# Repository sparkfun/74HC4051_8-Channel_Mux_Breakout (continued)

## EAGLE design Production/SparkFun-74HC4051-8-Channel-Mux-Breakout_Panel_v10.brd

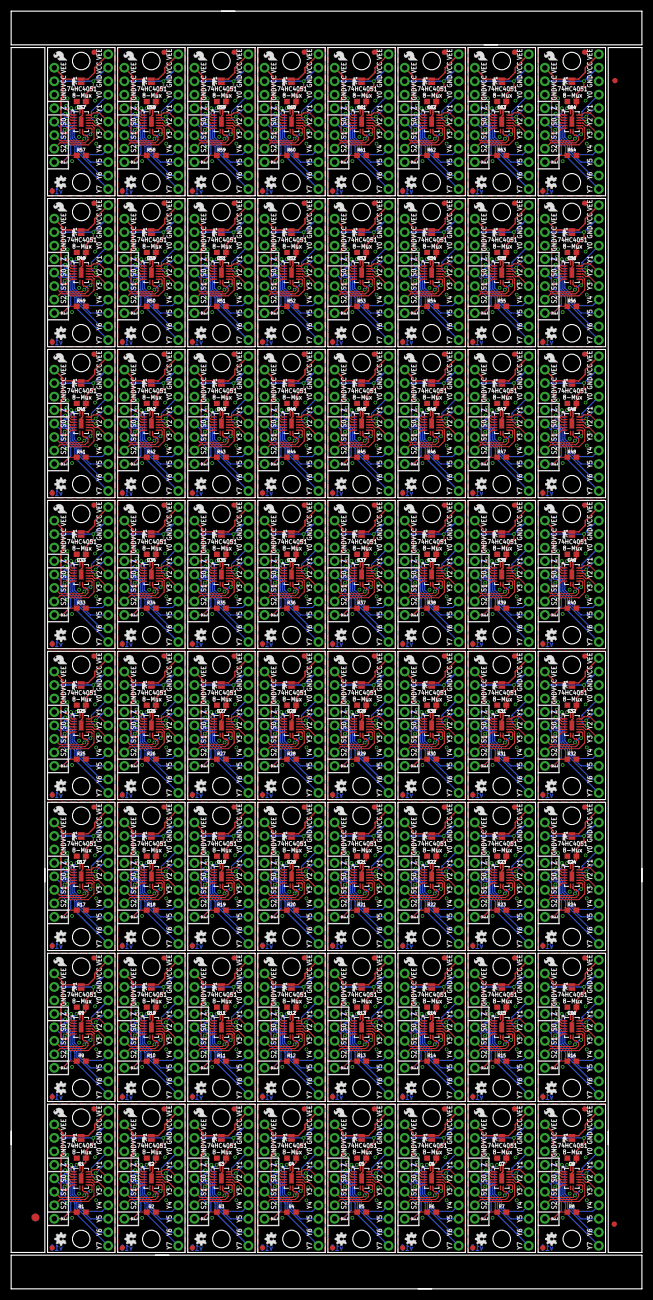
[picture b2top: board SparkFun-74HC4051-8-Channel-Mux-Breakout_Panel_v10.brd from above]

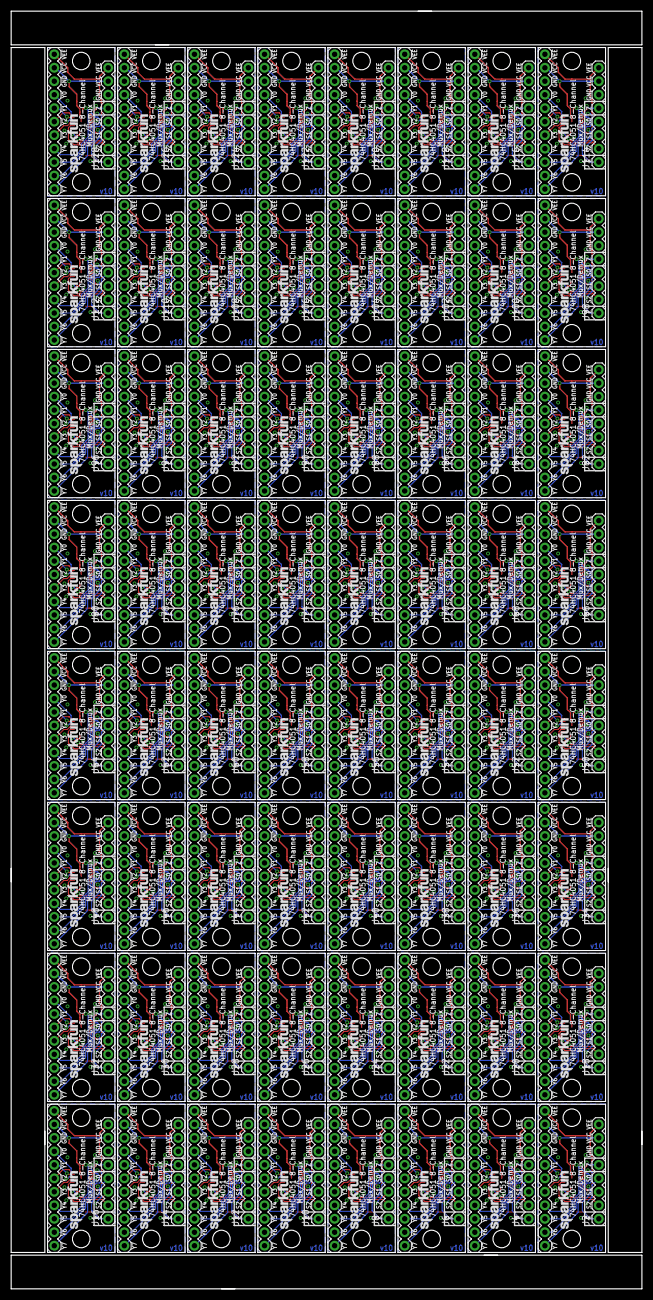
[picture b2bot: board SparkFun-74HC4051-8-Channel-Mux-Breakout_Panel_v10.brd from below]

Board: 2 copper layers, 118.9 x 240.8 mm, 835 parts (192 on the bottom side), 1024 nets.

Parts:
C1, C2, C3, C4, C5, C6, C7, C8, C9, C10, C11, C12, C13, C14, C15, C16, C17, C18, C19, C20, C21, C22, C23, C24, C25, C26, C27, C28, C29, C30, C31, C32, C33, C34, C35, C36, C37, C38, C39, C40, C41, C42, C43, C44, C45, C46, C47, C48, C49, C50, C51, C52, C53, C54, C55, C56, C57, C58, C59, C60, C61, C62, C63, C64: 0.1uF; 0603
E$1: FIDUCIAL-1.5X3
E$5, E$7: FIDUCIAL-1X2
FD1, FD2, FD3, FD4, FD5, FD6, FD7, FD8, FD9, FD10, FD11, FD12, FD13, FD14, FD15, FD16, FD17, FD18, FD19, FD20, FD21, FD22, FD23, FD24, FD25, FD26, FD27, FD28, FD29, FD30, FD31, FD32, FD33, FD34, FD35, FD36, FD37, FD38, FD39, FD40, FD41, FD42, FD43, FD44, FD45, FD46, FD47, FD48, FD49, FD50, FD51, FD52, FD53, FD54, FD55, FD56, FD57, FD58, FD59, FD60, FD61, FD62, FD63, FD64, FD65, FD66, FD67, FD68, FD69, FD70, FD71, FD72, FD73, FD74, FD75, FD76, FD77, FD78, FD79, FD80, FD81, FD82, FD83, FD84, FD85, FD86, FD87, FD88, FD89, FD90, FD91, FD92, FD93, FD94, FD95, FD96, FD97, FD98, FD99, FD100, FD101, FD102, FD103, FD104, FD105, FD106, FD107, FD108, FD109, FD110, FD111, FD112, FD113, FD114, FD115, FD116, FD117, FD118, FD119, FD120, FD121, FD122, FD123, FD124, FD125, FD126, FD127, FD128: FIDUCIAL1X2; FIDUCIAL-1X2
H1, H2, H3, H4, H5, H6, H7, H8, H9, H10, H11, H12, H13, H14, H15, H16, H17, H18, H19, H20, H21, H22, H23, H24, H25, H26, H27, H28, H29, H30, H31, H32, H33, H34, H35, H36, H37, H38, H39, H40, H41, H42, H43, H44, H45, H46, H47, H48, H49, H50, H51, H52, H53, H54, H55, H56, H57, H58, H59, H60, H61, H62, H63, H64, H65, H66, H67, H68, H69, H70, H71, H72, H73, H74, H75, H76, H77, H78, H79, H80, H81, H82, H83, H84, H85, H86, H87, H88, H89, H90, H91, H92, H93, H94, H95, H96, H97, H98, H99, H100, H101, H102, H103, H104, H105, H106, H107, H108, H109, H110, H111, H112, H113, H114, H115, H116, H117, H118, H119, H120, H121, H122, H123, H124, H125, H126, H127, H128: STAND-OFF
J1, J3, J5, J7, J9, J11, J13, J15, J17, J19, J21, J23, J25, J27, J29, J31, J33, J35, J37, J39, J41, J43, J45, J47, J49, J51, J53, J55, J57, J59, J61, J63, J65, J67, J69, J71, J73, J75, J77, J79, J81, J83, J85, J87, J89, J91, J93, J95, J97, J99, J101, J103, J105, J107, J109, J111, J113, J115, J117, J119, J121, J123, J125, J127: 1X11
J2, J4, J6, J8, J10, J12, J14, J16, J18, J20, J22, J24, J26, J28, J30, J32, J34, J36, J38, J40, J42, J44, J46, J48, J50, J52, J54, J56, J58, J60, J62, J64, J66, J68, J70, J72, J74, J76, J78, J80, J82, J84, J86, J88, J90, J92, J94, J96, J98, J100, J102, J104, J106, J108, J110, J112, J114, J116, J118, J120, J122, J124, J126, J128: 1X08_ROUND
JP1, JP2, JP3, JP4, JP5, JP6, JP7, JP8, JP9, JP10, JP11, JP12, JP13, JP14, JP15, JP16, JP17, JP18, JP19, JP20, JP21, JP22, JP23, JP24, JP25, JP26, JP27, JP28, JP29, JP30, JP31, JP32, JP33, JP34, JP35, JP36, JP37, JP38, JP39, JP40, JP41, JP42, JP43, JP44, JP45, JP46, JP47, JP48, JP49, JP50, JP51, JP52, JP53, JP54, JP55, JP56, JP57, JP58, JP59, JP60, JP61, JP62, JP63, JP64: VEE-GND; PAD-JUMPER-2-NC_BY_PASTE_NO_SILK
LOGO1, LOGO4, LOGO7, LOGO10, LOGO13, LOGO16, LOGO19, LOGO22, LOGO25, LOGO28, LOGO31, LOGO34, LOGO37, LOGO40, LOGO43, LOGO46, LOGO49, LOGO52, LOGO55, LOGO58, LOGO61, LOGO64, LOGO67, LOGO70, LOGO73, LOGO76, LOGO79, LOGO82, LOGO85, LOGO88, LOGO91, LOGO94, LOGO97, LOGO100, LOGO103, LOGO106, LOGO109, LOGO112, LOGO115, LOGO118, LOGO121, LOGO124, LOGO127, LOGO130, LOGO133, LOGO136, LOGO139, LOGO142, LOGO145, LOGO148, LOGO151, LOGO154, LOGO157, LOGO160, LOGO163, LOGO166, LOGO169, LOGO172, LOGO175, LOGO178, LOGO181, LOGO184, LOGO187, LOGO190: SFE_LOGO_FLAME.1_INCH; SFE_LOGO_FLAME_.1
LOGO2, LOGO5, LOGO8, LOGO11, LOGO14, LOGO17, LOGO20, LOGO23, LOGO26, LOGO29, LOGO32, LOGO35, LOGO38, LOGO41, LOGO44, LOGO47, LOGO50, LOGO53, LOGO56, LOGO59, LOGO62, LOGO65, LOGO68, LOGO71, LOGO74, LOGO77, LOGO80, LOGO83, LOGO86, LOGO89, LOGO92, LOGO95, LOGO98, LOGO101, LOGO104, LOGO107, LOGO110, LOGO113, LOGO116, LOGO119, LOGO122, LOGO125, LOGO128, LOGO131, LOGO134, LOGO137, LOGO140, LOGO143, LOGO146, LOGO149, LOGO152, LOGO155, LOGO158, LOGO161, LOGO164, LOGO167, LOGO170, LOGO173, LOGO176, LOGO179, LOGO182, LOGO185, LOGO188, LOGO191: OSHW-LOGOMINI; OSHW-LOGO-MINI
LOGO3, LOGO6, LOGO9, LOGO12, LOGO15, LOGO18, LOGO21, LOGO24, LOGO27, LOGO30, LOGO33, LOGO36, LOGO39, LOGO42, LOGO45, LOGO48, LOGO51, LOGO54, LOGO57, LOGO60, LOGO63, LOGO66, LOGO69, LOGO72, LOGO75, LOGO78, LOGO81, LOGO84, LOGO87, LOGO90, LOGO93, LOGO96, LOGO99, LOGO102, LOGO105, LOGO108, LOGO111, LOGO114, LOGO117, LOGO120, LOGO123, LOGO126, LOGO129, LOGO132, LOGO135, LOGO138, LOGO141, LOGO144, LOGO147, LOGO150, LOGO153, LOGO156, LOGO159, LOGO162, LOGO165, LOGO168, LOGO171, LOGO174, LOGO177, LOGO180, LOGO183, LOGO186, LOGO189, LOGO192: SFE_LOGO_NAME.1_INCH; SFE_LOGO_NAME_.1
R1, R2, R3, R4, R5, R6, R7, R8, R9, R10, R11, R12, R13, R14, R15, R16, R17, R18, R19, R20, R21, R22, R23, R24, R25, R26, R27, R28, R29, R30, R31, R32, R33, R34, R35, R36, R37, R38, R39, R40, R41, R42, R43, R44, R45, R46, R47, R48, R49, R50, R51, R52, R53, R54, R55, R56, R57, R58, R59, R60, R61, R62, R63, R64: 10k; 0603
U1, U2, U3, U4, U5, U6, U7, U8, U9, U10, U11, U12, U13, U14, U15, U16, U17, U18, U19, U20, U21, U22, U23, U24, U25, U26, U27, U28, U29, U30, U31, U32, U33, U34, U35, U36, U37, U38, U39, U40, U41, U42, U43, U44, U45, U46, U47, U48, U49, U50, U51, U52, U53, U54, U55, U56, U57, U58, U59, U60, U61, U62, U63, U64: 74HC4051BQ; DHVQFN-16-2.5X3.5MM

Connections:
!E!: J2.1, R1.1, U1.6
!E!1: J4.1, R2.1, U2.6
!E!2: J6.1, R3.1, U3.6
!E!3: J8.1, R4.1, U4.6
!E!4: J10.1, R5.1, U5.6
!E!5: J12.1, R6.1, U6.6
!E!6: J14.1, R7.1, U7.6
!E!7: J16.1, R8.1, U8.6
!E!8: J18.1, R9.1, U9.6
!E!9: J20.1, R10.1, U10.6
!E!10: J22.1, R11.1, U11.6
!E!11: J24.1, R12.1, U12.6
!E!12: J26.1, R13.1, U13.6
!E!13: J28.1, R14.1, U14.6
!E!14: J30.1, R15.1, U15.6
!E!15: J32.1, R16.1, U16.6
!E!16: J34.1, R17.1, U17.6
!E!17: J36.1, R18.1, U18.6
!E!18: J38.1, R19.1, U19.6
!E!19: J40.1, R20.1, U20.6
!E!20: J42.1, R21.1, U21.6
!E!21: J44.1, R22.1, U22.6
!E!22: J46.1, R23.1, U23.6
!E!23: J48.1, R24.1, U24.6
!E!24: J50.1, R25.1, U25.6
!E!25: J52.1, R26.1, U26.6
!E!26: J54.1, R27.1, U27.6
!E!27: J56.1, R28.1, U28.6
!E!28: J58.1, R29.1, U29.6
!E!29: J60.1, R30.1, U30.6
!E!30: J62.1, R31.1, U31.6
!E!31: J64.1, R32.1, U32.6
!E!32: J66.1, R33.1, U33.6
!E!33: J68.1, R34.1, U34.6
!E!34: J70.1, R35.1, U35.6
!E!35: J72.1, R36.1, U36.6
!E!36: J74.1, R37.1, U37.6
!E!37: J76.1, R38.1, U38.6
!E!38: J78.1, R39.1, U39.6
!E!39: J80.1, R40.1, U40.6
!E!40: J82.1, R41.1, U41.6
!E!41: J84.1, R42.1, U42.6
!E!42: J86.1, R43.1, U43.6
!E!43: J88.1, R44.1, U44.6
!E!44: J90.1, R45.1, U45.6
!E!45: J92.1, R46.1, U46.6
!E!46: J94.1, R47.1, U47.6
!E!47: J96.1, R48.1, U48.6
!E!48: J98.1, R49.1, U49.6
!E!49: J100.1, R50.1, U50.6
!E!50: J102.1, R51.1, U51.6
!E!51: J104.1, R52.1, U52.6
!E!52: J106.1, R53.1, U53.6
!E!53: J108.1, R54.1, U54.6
!E!54: J110.1, R55.1, U55.6
!E!55: J112.1, R56.1, U56.6
!E!56: J114.1, R57.1, U57.6
!E!57: J116.1, R58.1, U58.6
!E!58: J118.1, R59.1, U59.6
!E!59: J120.1, R60.1, U60.6
!E!60: J122.1, R61.1, U61.6
!E!61: J124.1, R62.1, U62.6
!E!62: J126.1, R63.1, U63.6
!E!63: J128.1, R64.1, U64.6
GND: C1.2, J1.9, J2.6, JP1.1, R1.2, U1.8
GND1: C2.2, J3.9, J4.6, JP2.1, R2.2, U2.8
GND2: C3.2, J5.9, J6.6, JP3.1, R3.2, U3.8
GND3: C4.2, J7.9, J8.6, JP4.1, R4.2, U4.8
GND4: C5.2, J9.9, J10.6, JP5.1, R5.2, U5.8
GND5: C6.2, J11.9, J12.6, JP6.1, R6.2, U6.8
GND6: C7.2, J13.9, J14.6, JP7.1, R7.2, U7.8
GND7: C8.2, J15.9, J16.6, JP8.1, R8.2, U8.8
GND8: C9.2, J17.9, J18.6, JP9.1, R9.2, U9.8
GND9: C10.2, J19.9, J20.6, JP10.1, R10.2, U10.8
GND10: C11.2, J21.9, J22.6, JP11.1, R11.2, U11.8
GND11: C12.2, J23.9, J24.6, JP12.1, R12.2, U12.8
GND12: C13.2, J25.9, J26.6, JP13.1, R13.2, U13.8
GND13: C14.2, J27.9, J28.6, JP14.1, R14.2, U14.8
GND14: C15.2, J29.9, J30.6, JP15.1, R15.2, U15.8
GND15: C16.2, J31.9, J32.6, JP16.1, R16.2, U16.8
GND16: C17.2, J33.9, J34.6, JP17.1, R17.2, U17.8
GND17: C18.2, J35.9, J36.6, JP18.1, R18.2, U18.8
GND18: C19.2, J37.9, J38.6, JP19.1, R19.2, U19.8
GND19: C20.2, J39.9, J40.6, JP20.1, R20.2, U20.8
GND20: C21.2, J41.9, J42.6, JP21.1, R21.2, U21.8
GND21: C22.2, J43.9, J44.6, JP22.1, R22.2, U22.8
GND22: C23.2, J45.9, J46.6, JP23.1, R23.2, U23.8
GND23: C24.2, J47.9, J48.6, JP24.1, R24.2, U24.8
GND24: C25.2, J49.9, J50.6, JP25.1, R25.2, U25.8
GND25: C26.2, J51.9, J52.6, JP26.1, R26.2, U26.8
GND26: C27.2, J53.9, J54.6, JP27.1, R27.2, U27.8
GND27: C28.2, J55.9, J56.6, JP28.1, R28.2, U28.8
GND28: C29.2, J57.9, J58.6, JP29.1, R29.2, U29.8
GND29: C30.2, J59.9, J60.6, JP30.1, R30.2, U30.8
GND30: C31.2, J61.9, J62.6, JP31.1, R31.2, U31.8
GND31: C32.2, J63.9, J64.6, JP32.1, R32.2, U32.8
GND32: C33.2, J65.9, J66.6, JP33.1, R33.2, U33.8
GND33: C34.2, J67.9, J68.6, JP34.1, R34.2, U34.8
GND34: C35.2, J69.9, J70.6, JP35.1, R35.2, U35.8
GND35: C36.2, J71.9, J72.6, JP36.1, R36.2, U36.8
GND36: C37.2, J73.9, J74.6, JP37.1, R37.2, U37.8
GND37: C38.2, J75.9, J76.6, JP38.1, R38.2, U38.8
GND38: C39.2, J77.9, J78.6, JP39.1, R39.2, U39.8
GND39: C40.2, J79.9, J80.6, JP40.1, R40.2, U40.8
GND40: C41.2, J81.9, J82.6, JP41.1, R41.2, U41.8
GND41: C42.2, J83.9, J84.6, JP42.1, R42.2, U42.8
GND42: C43.2, J85.9, J86.6, JP43.1, R43.2, U43.8
GND43: C44.2, J87.9, J88.6, JP44.1, R44.2, U44.8
GND44: C45.2, J89.9, J90.6, JP45.1, R45.2, U45.8
GND45: C46.2, J91.9, J92.6, JP46.1, R46.2, U46.8
GND46: C47.2, J93.9, J94.6, JP47.1, R47.2, U47.8
GND47: C48.2, J95.9, J96.6, JP48.1, R48.2, U48.8
GND48: C49.2, J97.9, J98.6, JP49.1, R49.2, U49.8
GND49: C50.2, J99.9, J100.6, JP50.1, R50.2, U50.8
GND50: C51.2, J101.9, J102.6, JP51.1, R51.2, U51.8
GND51: C52.2, J103.9, J104.6, JP52.1, R52.2, U52.8
GND52: C53.2, J105.9, J106.6, JP53.1, R53.2, U53.8
GND53: C54.2, J107.9, J108.6, JP54.1, R54.2, U54.8
GND54: C55.2, J109.9, J110.6, JP55.1, R55.2, U55.8
GND55: C56.2, J111.9, J112.6, JP56.1, R56.2, U56.8
GND56: C57.2, J113.9, J114.6, JP57.1, R57.2, U57.8
GND57: C58.2, J115.9, J116.6, JP58.1, R58.2, U58.8
GND58: C59.2, J117.9, J118.6, JP59.1, R59.2, U59.8
GND59: C60.2, J119.9, J120.6, JP60.1, R60.2, U60.8
GND60: C61.2, J121.9, J122.6, JP61.1, R61.2, U61.8
GND61: C62.2, J123.9, J124.6, JP62.1, R62.2, U62.8
GND62: C63.2, J125.9, J126.6, JP63.1, R63.2, U63.8
GND63: C64.2, J127.9, J128.6, JP64.1, R64.2, U64.8
S0: J2.4, U1.11
S1: J2.3, U1.10
S2: J2.2, U1.9
S3: J4.2, U2.9
S4: J4.4, U2.11
S5: J4.3, U2.10
S6: J6.2, U3.9
S7: J6.4, U3.11
S8: J6.3, U3.10
S9: J8.2, U4.9
S10: J8.4, U4.11
S11: J8.3, U4.10
S12: J10.2, U5.9
S13: J10.4, U5.11
S14: J10.3, U5.10
S15: J12.2, U6.9
S16: J12.4, U6.11
S17: J12.3, U6.10
S18: J14.2, U7.9
S19: J14.4, U7.11
S20: J14.3, U7.10
S21: J16.2, U8.9
S22: J16.4, U8.11
S23: J16.3, U8.10
S24: J18.2, U9.9
S25: J18.4, U9.11
S26: J18.3, U9.10
S27: J20.2, U10.9
S28: J20.4, U10.11
S29: J20.3, U10.10
S30: J22.2, U11.9
S31: J22.4, U11.11
S32: J22.3, U11.10
S33: J24.2, U12.9
S34: J24.4, U12.11
S35: J24.3, U12.10
S36: J26.2, U13.9
S37: J26.4, U13.11
S38: J26.3, U13.10
S39: J28.2, U14.9
S40: J28.4, U14.11
S41: J28.3, U14.10
S42: J30.2, U15.9
S43: J30.4, U15.11
S44: J30.3, U15.10
S45: J32.2, U16.9
S46: J32.4, U16.11
S47: J32.3, U16.10
S48: J34.2, U17.9
S49: J34.4, U17.11
S50: J34.3, U17.10
S51: J36.2, U18.9
S52: J36.4, U18.11
S53: J36.3, U18.10
S54: J38.2, U19.9
S55: J38.4, U19.11
S56: J38.3, U19.10
S57: J40.2, U20.9
S58: J40.4, U20.11
S59: J40.3, U20.10
S60: J42.2, U21.9
S61: J42.4, U21.11
S62: J42.3, U21.10
S63: J44.2, U22.9
S64: J44.4, U22.11
S65: J44.3, U22.10
S66: J46.2, U23.9
S67: J46.4, U23.11
S68: J46.3, U23.10
S69: J48.2, U24.9
S70: J48.4, U24.11
S71: J48.3, U24.10
S72: J50.2, U25.9
S73: J50.4, U25.11
S74: J50.3, U25.10
S75: J52.2, U26.9
S76: J52.4, U26.11
S77: J52.3, U26.10
S78: J54.2, U27.9
S79: J54.4, U27.11
S80: J54.3, U27.10
S81: J56.2, U28.9
S82: J56.4, U28.11
S83: J56.3, U28.10
S84: J58.2, U29.9
S85: J58.4, U29.11
S86: J58.3, U29.10
S87: J60.2, U30.9
S88: J60.4, U30.11
S89: J60.3, U30.10
S90: J62.2, U31.9
S91: J62.4, U31.11
S92: J62.3, U31.10
S93: J64.2, U32.9
S94: J64.4, U32.11
S95: J64.3, U32.10
S96: J66.2, U33.9
S97: J66.4, U33.11
S98: J66.3, U33.10
S99: J68.2, U34.9
S100: J68.4, U34.11
S101: J68.3, U34.10
S102: J70.2, U35.9
S103: J70.4, U35.11
S104: J70.3, U35.10
S105: J72.2, U36.9
S106: J72.4, U36.11
S107: J72.3, U36.10
S108: J74.2, U37.9
S109: J74.4, U37.11
S110: J74.3, U37.10
S111: J76.2, U38.9
S112: J76.4, U38.11
S113: J76.3, U38.10
S114: J78.2, U39.9
S115: J78.4, U39.11
S116: J78.3, U39.10
S117: J80.2, U40.9
S118: J80.4, U40.11
S119: J80.3, U40.10
S120: J82.2, U41.9
S121: J82.4, U41.11
S122: J82.3, U41.10
S123: J84.2, U42.9
S124: J84.4, U42.11
S125: J84.3, U42.10
S126: J86.2, U43.9
S127: J86.4, U43.11
S128: J86.3, U43.10
S129: J88.2, U44.9
S130: J88.4, U44.11
S131: J88.3, U44.10
S132: J90.2, U45.9
S133: J90.4, U45.11
S134: J90.3, U45.10
S135: J92.2, U46.9
S136: J92.4, U46.11
S137: J92.3, U46.10
S138: J94.2, U47.9
S139: J94.4, U47.11
S140: J94.3, U47.10
S141: J96.2, U48.9
S142: J96.4, U48.11
S143: J96.3, U48.10
S144: J98.2, U49.9
S145: J98.4, U49.11
S146: J98.3, U49.10
S147: J100.2, U50.9
S148: J100.4, U50.11
S149: J100.3, U50.10
S150: J102.2, U51.9
S151: J102.4, U51.11
S152: J102.3, U51.10
S153: J104.2, U52.9
S154: J104.4, U52.11
S155: J104.3, U52.10
S156: J106.2, U53.9
S157: J106.4, U53.11
S158: J106.3, U53.10
S159: J108.2, U54.9
S160: J108.4, U54.11
S161: J108.3, U54.10
S162: J110.2, U55.9
S163: J110.4, U55.11
S164: J110.3, U55.10
S165: J112.2, U56.9
S166: J112.4, U56.11
S167: J112.3, U56.10
S168: J114.2, U57.9
S169: J114.4, U57.11
S170: J114.3, U57.10
S171: J116.2, U58.9
S172: J116.4, U58.11
S173: J116.3, U58.10
S174: J118.2, U59.9
S175: J118.4, U59.11
S176: J118.3, U59.10
S177: J120.2, U60.9
S178: J120.4, U60.11
S179: J120.3, U60.10
S180: J122.2, U61.9
S181: J122.4, U61.11
S182: J122.3, U61.10
S183: J124.2, U62.9
S184: J124.4, U62.11
S185: J124.3, U62.10
S186: J126.2, U63.9
S187: J126.4, U63.11
S188: J126.3, U63.10
S189: J128.2, U64.9
S190: J128.4, U64.11
S191: J128.3, U64.10
VCC: C1.1, J1.10, J2.7, U1.16, U1.EP
VCC1: C2.1, J3.10, J4.7, U2.16, U2.EP
VCC2: C3.1, J5.10, J6.7, U3.16, U3.EP
VCC3: C4.1, J7.10, J8.7, U4.16, U4.EP
VCC4: C5.1, J9.10, J10.7, U5.16, U5.EP
VCC5: C6.1, J11.10, J12.7, U6.16, U6.EP
VCC6: C7.1, J13.10, J14.7, U7.16, U7.EP
VCC7: C8.1, J15.10, J16.7, U8.16, U8.EP
VCC8: C9.1, J17.10, J18.7, U9.16, U9.EP
VCC9: C10.1, J19.10, J20.7, U10.16, U10.EP
VCC10: C11.1, J21.10, J22.7, U11.16, U11.EP
VCC11: C12.1, J23.10, J24.7, U12.16, U12.EP
VCC12: C13.1, J25.10, J26.7, U13.16, U13.EP
VCC13: C14.1, J27.10, J28.7, U14.16, U14.EP
VCC14: C15.1, J29.10, J30.7, U15.16, U15.EP
VCC15: C16.1, J31.10, J32.7, U16.16, U16.EP
VCC16: C17.1, J33.10, J34.7, U17.16, U17.EP
VCC17: C18.1, J35.10, J36.7, U18.16, U18.EP
VCC18: C19.1, J37.10, J38.7, U19.16, U19.EP
VCC19: C20.1, J39.10, J40.7, U20.16, U20.EP
VCC20: C21.1, J41.10, J42.7, U21.16, U21.EP
VCC21: C22.1, J43.10, J44.7, U22.16, U22.EP
VCC22: C23.1, J45.10, J46.7, U23.16, U23.EP
VCC23: C24.1, J47.10, J48.7, U24.16, U24.EP
VCC24: C25.1, J49.10, J50.7, U25.16, U25.EP
VCC25: C26.1, J51.10, J52.7, U26.16, U26.EP
VCC26: C27.1, J53.10, J54.7, U27.16, U27.EP
VCC27: C28.1, J55.10, J56.7, U28.16, U28.EP
VCC28: C29.1, J57.10, J58.7, U29.16, U29.EP
VCC29: C30.1, J59.10, J60.7, U30.16, U30.EP
VCC30: C31.1, J61.10, J62.7, U31.16, U31.EP
VCC31: C32.1, J63.10, J64.7, U32.16, U32.EP
VCC32: C33.1, J65.10, J66.7, U33.16, U33.EP
VCC33: C34.1, J67.10, J68.7, U34.16, U34.EP
VCC34: C35.1, J69.10, J70.7, U35.16, U35.EP
VCC35: C36.1, J71.10, J72.7, U36.16, U36.EP
VCC36: C37.1, J73.10, J74.7, U37.16, U37.EP
VCC37: C38.1, J75.10, J76.7, U38.16, U38.EP
VCC38: C39.1, J77.10, J78.7, U39.16, U39.EP
VCC39: C40.1, J79.10, J80.7, U40.16, U40.EP
VCC40: C41.1, J81.10, J82.7, U41.16, U41.EP
VCC41: C42.1, J83.10, J84.7, U42.16, U42.EP
VCC42: C43.1, J85.10, J86.7, U43.16, U43.EP
VCC43: C44.1, J87.10, J88.7, U44.16, U44.EP
VCC44: C45.1, J89.10, J90.7, U45.16, U45.EP
VCC45: C46.1, J91.10, J92.7, U46.16, U46.EP
VCC46: C47.1, J93.10, J94.7, U47.16, U47.EP
VCC47: C48.1, J95.10, J96.7, U48.16, U48.EP
VCC48: C49.1, J97.10, J98.7, U49.16, U49.EP
VCC49: C50.1, J99.10, J100.7, U50.16, U50.EP
VCC50: C51.1, J101.10, J102.7, U51.16, U51.EP
VCC51: C52.1, J103.10, J104.7, U52.16, U52.EP
VCC52: C53.1, J105.10, J106.7, U53.16, U53.EP
VCC53: C54.1, J107.10, J108.7, U54.16, U54.EP
VCC54: C55.1, J109.10, J110.7, U55.16, U55.EP
VCC55: C56.1, J111.10, J112.7, U56.16, U56.EP
VCC56: C57.1, J113.10, J114.7, U57.16, U57.EP
VCC57: C58.1, J115.10, J116.7, U58.16, U58.EP
VCC58: C59.1, J117.10, J118.7, U59.16, U59.EP
VCC59: C60.1, J119.10, J120.7, U60.16, U60.EP
VCC60: C61.1, J121.10, J122.7, U61.16, U61.EP
VCC61: C62.1, J123.10, J124.7, U62.16, U62.EP
VCC62: C63.1, J125.10, J126.7, U63.16, U63.EP
VCC63: C64.1, J127.10, J128.7, U64.16, U64.EP
VEE: J1.11, J2.8, JP1.2, U1.7
VEE1: J3.11, J4.8, JP2.2, U2.7
VEE2: J5.11, J6.8, JP3.2, U3.7
VEE3: J7.11, J8.8, JP4.2, U4.7
VEE4: J9.11, J10.8, JP5.2, U5.7
VEE5: J11.11, J12.8, JP6.2, U6.7
VEE6: J13.11, J14.8, JP7.2, U7.7
VEE7: J15.11, J16.8, JP8.2, U8.7
VEE8: J17.11, J18.8, JP9.2, U9.7
VEE9: J19.11, J20.8, JP10.2, U10.7
VEE10: J21.11, J22.8, JP11.2, U11.7
VEE11: J23.11, J24.8, JP12.2, U12.7
VEE12: J25.11, J26.8, JP13.2, U13.7
VEE13: J27.11, J28.8, JP14.2, U14.7
VEE14: J29.11, J30.8, JP15.2, U15.7
VEE15: J31.11, J32.8, JP16.2, U16.7
VEE16: J33.11, J34.8, JP17.2, U17.7
VEE17: J35.11, J36.8, JP18.2, U18.7
VEE18: J37.11, J38.8, JP19.2, U19.7
VEE19: J39.11, J40.8, JP20.2, U20.7
VEE20: J41.11, J42.8, JP21.2, U21.7
VEE21: J43.11, J44.8, JP22.2, U22.7
VEE22: J45.11, J46.8, JP23.2, U23.7
VEE23: J47.11, J48.8, JP24.2, U24.7
VEE24: J49.11, J50.8, JP25.2, U25.7
VEE25: J51.11, J52.8, JP26.2, U26.7
VEE26: J53.11, J54.8, JP27.2, U27.7
VEE27: J55.11, J56.8, JP28.2, U28.7
VEE28: J57.11, J58.8, JP29.2, U29.7
VEE29: J59.11, J60.8, JP30.2, U30.7
VEE30: J61.11, J62.8, JP31.2, U31.7
VEE31: J63.11, J64.8, JP32.2, U32.7
VEE32: J65.11, J66.8, JP33.2, U33.7
VEE33: J67.11, J68.8, JP34.2, U34.7
VEE34: J69.11, J70.8, JP35.2, U35.7
VEE35: J71.11, J72.8, JP36.2, U36.7
VEE36: J73.11, J74.8, JP37.2, U37.7
VEE37: J75.11, J76.8, JP38.2, U38.7
VEE38: J77.11, J78.8, JP39.2, U39.7
VEE39: J79.11, J80.8, JP40.2, U40.7
VEE40: J81.11, J82.8, JP41.2, U41.7
VEE41: J83.11, J84.8, JP42.2, U42.7
VEE42: J85.11, J86.8, JP43.2, U43.7
VEE43: J87.11, J88.8, JP44.2, U44.7
VEE44: J89.11, J90.8, JP45.2, U45.7
VEE45: J91.11, J92.8, JP46.2, U46.7
VEE46: J93.11, J94.8, JP47.2, U47.7
VEE47: J95.11, J96.8, JP48.2, U48.7
VEE48: J97.11, J98.8, JP49.2, U49.7
VEE49: J99.11, J100.8, JP50.2, U50.7
VEE50: J101.11, J102.8, JP51.2, U51.7
VEE51: J103.11, J104.8, JP52.2, U52.7
VEE52: J105.11, J106.8, JP53.2, U53.7
VEE53: J107.11, J108.8, JP54.2, U54.7
VEE54: J109.11, J110.8, JP55.2, U55.7
VEE55: J111.11, J112.8, JP56.2, U56.7
VEE56: J113.11, J114.8, JP57.2, U57.7
VEE57: J115.11, J116.8, JP58.2, U58.7
VEE58: J117.11, J118.8, JP59.2, U59.7
VEE59: J119.11, J120.8, JP60.2, U60.7
VEE60: J121.11, J122.8, JP61.2, U61.7
VEE61: J123.11, J124.8, JP62.2, U62.7
VEE62: J125.11, J126.8, JP63.2, U63.7
VEE63: J127.11, J128.8, JP64.2, U64.7
Y0: J1.8, U1.13
Y1: J1.7, U1.14
Y2: J1.6, U1.15
Y3: J1.5, U1.12
Y4: J1.4, U1.1
Y5: J1.3, U1.5
Y6: J1.2, U1.2
Y7: J1.1, U1.4
Y8: J3.1, U2.4
Y9: J3.2, U2.2
Y10: J3.3, U2.5
Y11: J3.4, U2.1
Y12: J3.5, U2.12
Y13: J3.6, U2.15
Y14: J3.7, U2.14
Y15: J3.8, U2.13
Y16: J5.1, U3.4
Y17: J5.2, U3.2
Y18: J5.3, U3.5
Y19: J5.4, U3.1
Y20: J5.5, U3.12
Y21: J5.6, U3.15
Y22: J5.7, U3.14
Y23: J5.8, U3.13
Y24: J7.1, U4.4
Y25: J7.2, U4.2
Y26: J7.3, U4.5
Y27: J7.4, U4.1
Y28: J7.5, U4.12
Y29: J7.6, U4.15
Y30: J7.7, U4.14
Y31: J7.8, U4.13
Y32: J9.1, U5.4
Y33: J9.2, U5.2
Y34: J9.3, U5.5
Y35: J9.4, U5.1
Y36: J9.5, U5.12
Y37: J9.6, U5.15
Y38: J9.7, U5.14
Y39: J9.8, U5.13
Y40: J11.1, U6.4
Y41: J11.2, U6.2
Y42: J11.3, U6.5
Y43: J11.4, U6.1
Y44: J11.5, U6.12
Y45: J11.6, U6.15
Y46: J11.7, U6.14
Y47: J11.8, U6.13
Y48: J13.1, U7.4
Y49: J13.2, U7.2
Y50: J13.3, U7.5
Y51: J13.4, U7.1
Y52: J13.5, U7.12
Y53: J13.6, U7.15
Y54: J13.7, U7.14
Y55: J13.8, U7.13
Y56: J15.1, U8.4
Y57: J15.2, U8.2
Y58: J15.3, U8.5
Y59: J15.4, U8.1
Y60: J15.5, U8.12
Y61: J15.6, U8.15
Y62: J15.7, U8.14
Y63: J15.8, U8.13
Y64: J17.1, U9.4
Y65: J17.2, U9.2
Y66: J17.3, U9.5
Y67: J17.4, U9.1
Y68: J17.5, U9.12
Y69: J17.6, U9.15
Y70: J17.7, U9.14
Y71: J17.8, U9.13
Y72: J19.1, U10.4
Y73: J19.2, U10.2
Y74: J19.3, U10.5
Y75: J19.4, U10.1
Y76: J19.5, U10.12
Y77: J19.6, U10.15
Y78: J19.7, U10.14
Y79: J19.8, U10.13
Y80: J21.1, U11.4
Y81: J21.2, U11.2
Y82: J21.3, U11.5
Y83: J21.4, U11.1
Y84: J21.5, U11.12
Y85: J21.6, U11.15
Y86: J21.7, U11.14
Y87: J21.8, U11.13
Y88: J23.1, U12.4
Y89: J23.2, U12.2
Y90: J23.3, U12.5
Y91: J23.4, U12.1
Y92: J23.5, U12.12
Y93: J23.6, U12.15
Y94: J23.7, U12.14
Y95: J23.8, U12.13
Y96: J25.1, U13.4
Y97: J25.2, U13.2
Y98: J25.3, U13.5
Y99: J25.4, U13.1
Y100: J25.5, U13.12
Y101: J25.6, U13.15
Y102: J25.7, U13.14
Y103: J25.8, U13.13
Y104: J27.1, U14.4
Y105: J27.2, U14.2
Y106: J27.3, U14.5
Y107: J27.4, U14.1
Y108: J27.5, U14.12
Y109: J27.6, U14.15
Y110: J27.7, U14.14
Y111: J27.8, U14.13
Y112: J29.1, U15.4
Y113: J29.2, U15.2
Y114: J29.3, U15.5
Y115: J29.4, U15.1
Y116: J29.5, U15.12
Y117: J29.6, U15.15
Y118: J29.7, U15.14
Y119: J29.8, U15.13
Y120: J31.1, U16.4
Y121: J31.2, U16.2
Y122: J31.3, U16.5
Y123: J31.4, U16.1
Y124: J31.5, U16.12
Y125: J31.6, U16.15
Y126: J31.7, U16.14
Y127: J31.8, U16.13
Y128: J33.1, U17.4
Y129: J33.2, U17.2
Y130: J33.3, U17.5
Y131: J33.4, U17.1
Y132: J33.5, U17.12
Y133: J33.6, U17.15
Y134: J33.7, U17.14
Y135: J33.8, U17.13
Y136: J35.1, U18.4
Y137: J35.2, U18.2
Y138: J35.3, U18.5
Y139: J35.4, U18.1
Y140: J35.5, U18.12
Y141: J35.6, U18.15
Y142: J35.7, U18.14
Y143: J35.8, U18.13
Y144: J37.1, U19.4
Y145: J37.2, U19.2
Y146: J37.3, U19.5
Y147: J37.4, U19.1
Y148: J37.5, U19.12
Y149: J37.6, U19.15
Y150: J37.7, U19.14
Y151: J37.8, U19.13
Y152: J39.1, U20.4
Y153: J39.2, U20.2
Y154: J39.3, U20.5
Y155: J39.4, U20.1
Y156: J39.5, U20.12
Y157: J39.6, U20.15
Y158: J39.7, U20.14
Y159: J39.8, U20.13
Y160: J41.1, U21.4
Y161: J41.2, U21.2
Y162: J41.3, U21.5
Y163: J41.4, U21.1
Y164: J41.5, U21.12
Y165: J41.6, U21.15
Y166: J41.7, U21.14
Y167: J41.8, U21.13
Y168: J43.1, U22.4
Y169: J43.2, U22.2
Y170: J43.3, U22.5
Y171: J43.4, U22.1
Y172: J43.5, U22.12
Y173: J43.6, U22.15
Y174: J43.7, U22.14
Y175: J43.8, U22.13
Y176: J45.1, U23.4
Y177: J45.2, U23.2
Y178: J45.3, U23.5
Y179: J45.4, U23.1
Y180: J45.5, U23.12
Y181: J45.6, U23.15
Y182: J45.7, U23.14
Y183: J45.8, U23.13
Y184: J47.1, U24.4
Y185: J47.2, U24.2
Y186: J47.3, U24.5
Y187: J47.4, U24.1
Y188: J47.5, U24.12
Y189: J47.6, U24.15
Y190: J47.7, U24.14
Y191: J47.8, U24.13
Y192: J49.1, U25.4
Y193: J49.2, U25.2
Y194: J49.3, U25.5
Y195: J49.4, U25.1
Y196: J49.5, U25.12
Y197: J49.6, U25.15
Y198: J49.7, U25.14
Y199: J49.8, U25.13
Y200: J51.1, U26.4
Y201: J51.2, U26.2
Y202: J51.3, U26.5
Y203: J51.4, U26.1
Y204: J51.5, U26.12
Y205: J51.6, U26.15
Y206: J51.7, U26.14
Y207: J51.8, U26.13
Y208: J53.1, U27.4
Y209: J53.2, U27.2
Y210: J53.3, U27.5
Y211: J53.4, U27.1
Y212: J53.5, U27.12
Y213: J53.6, U27.15
Y214: J53.7, U27.14
Y215: J53.8, U27.13
Y216: J55.1, U28.4
Y217: J55.2, U28.2
Y218: J55.3, U28.5
Y219: J55.4, U28.1
Y220: J55.5, U28.12
Y221: J55.6, U28.15
Y222: J55.7, U28.14
Y223: J55.8, U28.13
Y224: J57.1, U29.4
Y225: J57.2, U29.2
Y226: J57.3, U29.5
Y227: J57.4, U29.1
Y228: J57.5, U29.12
Y229: J57.6, U29.15
Y230: J57.7, U29.14
Y231: J57.8, U29.13
Y232: J59.1, U30.4
Y233: J59.2, U30.2
Y234: J59.3, U30.5
Y235: J59.4, U30.1
Y236: J59.5, U30.12
Y237: J59.6, U30.15
Y238: J59.7, U30.14
Y239: J59.8, U30.13
Y240: J61.1, U31.4
Y241: J61.2, U31.2
Y242: J61.3, U31.5
Y243: J61.4, U31.1
Y244: J61.5, U31.12
Y245: J61.6, U31.15
Y246: J61.7, U31.14
Y247: J61.8, U31.13
Y248: J63.1, U32.4
Y249: J63.2, U32.2
Y250: J63.3, U32.5
Y251: J63.4, U32.1
Y252: J63.5, U32.12
Y253: J63.6, U32.15
Y254: J63.7, U32.14
Y255: J63.8, U32.13
Y256: J65.1, U33.4
Y257: J65.2, U33.2
Y258: J65.3, U33.5
Y259: J65.4, U33.1
Y260: J65.5, U33.12
Y261: J65.6, U33.15
Y262: J65.7, U33.14
Y263: J65.8, U33.13
Y264: J67.1, U34.4
Y265: J67.2, U34.2
Y266: J67.3, U34.5
Y267: J67.4, U34.1
Y268: J67.5, U34.12
Y269: J67.6, U34.15
Y270: J67.7, U34.14
Y271: J67.8, U34.13
Y272: J69.1, U35.4
Y273: J69.2, U35.2
Y274: J69.3, U35.5
Y275: J69.4, U35.1
Y276: J69.5, U35.12
Y277: J69.6, U35.15
Y278: J69.7, U35.14
Y279: J69.8, U35.13
Y280: J71.1, U36.4
Y281: J71.2, U36.2
Y282: J71.3, U36.5
Y283: J71.4, U36.1
Y284: J71.5, U36.12
Y285: J71.6, U36.15
Y286: J71.7, U36.14
Y287: J71.8, U36.13
Y288: J73.1, U37.4
Y289: J73.2, U37.2
Y290: J73.3, U37.5
Y291: J73.4, U37.1
Y292: J73.5, U37.12
Y293: J73.6, U37.15
Y294: J73.7, U37.14
Y295: J73.8, U37.13
Y296: J75.1, U38.4
Y297: J75.2, U38.2
Y298: J75.3, U38.5
Y299: J75.4, U38.1
Y300: J75.5, U38.12
Y301: J75.6, U38.15
Y302: J75.7, U38.14
Y303: J75.8, U38.13
Y304: J77.1, U39.4
Y305: J77.2, U39.2
Y306: J77.3, U39.5
Y307: J77.4, U39.1
Y308: J77.5, U39.12
Y309: J77.6, U39.15
Y310: J77.7, U39.14
Y311: J77.8, U39.13
Y312: J79.1, U40.4
Y313: J79.2, U40.2
Y314: J79.3, U40.5
Y315: J79.4, U40.1
Y316: J79.5, U40.12
Y317: J79.6, U40.15
Y318: J79.7, U40.14
Y319: J79.8, U40.13
Y320: J81.1, U41.4
Y321: J81.2, U41.2
Y322: J81.3, U41.5
Y323: J81.4, U41.1
Y324: J81.5, U41.12
Y325: J81.6, U41.15
Y326: J81.7, U41.14
Y327: J81.8, U41.13
Y328: J83.1, U42.4
Y329: J83.2, U42.2
Y330: J83.3, U42.5
Y331: J83.4, U42.1
Y332: J83.5, U42.12
Y333: J83.6, U42.15
Y334: J83.7, U42.14
Y335: J83.8, U42.13
Y336: J85.1, U43.4
Y337: J85.2, U43.2
Y338: J85.3, U43.5
Y339: J85.4, U43.1
Y340: J85.5, U43.12
Y341: J85.6, U43.15
Y342: J85.7, U43.14
Y343: J85.8, U43.13
Y344: J87.1, U44.4
Y345: J87.2, U44.2
Y346: J87.3, U44.5
Y347: J87.4, U44.1
Y348: J87.5, U44.12
Y349: J87.6, U44.15
Y350: J87.7, U44.14
Y351: J87.8, U44.13
Y352: J89.1, U45.4
Y353: J89.2, U45.2
Y354: J89.3, U45.5
Y355: J89.4, U45.1
Y356: J89.5, U45.12
Y357: J89.6, U45.15
Y358: J89.7, U45.14
Y359: J89.8, U45.13
Y360: J91.1, U46.4
Y361: J91.2, U46.2
Y362: J91.3, U46.5
Y363: J91.4, U46.1
Y364: J91.5, U46.12
Y365: J91.6, U46.15
Y366: J91.7, U46.14
Y367: J91.8, U46.13
Y368: J93.1, U47.4
Y369: J93.2, U47.2
Y370: J93.3, U47.5
Y371: J93.4, U47.1
Y372: J93.5, U47.12
Y373: J93.6, U47.15
Y374: J93.7, U47.14
Y375: J93.8, U47.13
Y376: J95.1, U48.4
Y377: J95.2, U48.2
Y378: J95.3, U48.5
Y379: J95.4, U48.1
Y380: J95.5, U48.12
Y381: J95.6, U48.15
Y382: J95.7, U48.14
Y383: J95.8, U48.13
Y384: J97.1, U49.4
Y385: J97.2, U49.2
Y386: J97.3, U49.5
Y387: J97.4, U49.1
Y388: J97.5, U49.12
Y389: J97.6, U49.15
Y390: J97.7, U49.14
Y391: J97.8, U49.13
Y392: J99.1, U50.4
Y393: J99.2, U50.2
Y394: J99.3, U50.5
Y395: J99.4, U50.1
Y396: J99.5, U50.12
Y397: J99.6, U50.15
Y398: J99.7, U50.14
Y399: J99.8, U50.13
Y400: J101.1, U51.4
Y401: J101.2, U51.2
Y402: J101.3, U51.5
Y403: J101.4, U51.1
Y404: J101.5, U51.12
Y405: J101.6, U51.15
Y406: J101.7, U51.14
Y407: J101.8, U51.13
Y408: J103.1, U52.4
Y409: J103.2, U52.2
Y410: J103.3, U52.5
Y411: J103.4, U52.1
Y412: J103.5, U52.12
Y413: J103.6, U52.15
Y414: J103.7, U52.14
Y415: J103.8, U52.13
Y416: J105.1, U53.4
Y417: J105.2, U53.2
Y418: J105.3, U53.5
Y419: J105.4, U53.1
Y420: J105.5, U53.12
Y421: J105.6, U53.15
Y422: J105.7, U53.14
Y423: J105.8, U53.13
Y424: J107.1, U54.4
Y425: J107.2, U54.2
Y426: J107.3, U54.5
Y427: J107.4, U54.1
Y428: J107.5, U54.12
Y429: J107.6, U54.15
Y430: J107.7, U54.14
Y431: J107.8, U54.13
Y432: J109.1, U55.4
Y433: J109.2, U55.2
Y434: J109.3, U55.5
Y435: J109.4, U55.1
Y436: J109.5, U55.12
Y437: J109.6, U55.15
Y438: J109.7, U55.14
Y439: J109.8, U55.13
Y440: J111.1, U56.4
Y441: J111.2, U56.2
Y442: J111.3, U56.5
Y443: J111.4, U56.1
Y444: J111.5, U56.12
Y445: J111.6, U56.15
Y446: J111.7, U56.14
Y447: J111.8, U56.13
Y448: J113.1, U57.4
Y449: J113.2, U57.2
Y450: J113.3, U57.5
Y451: J113.4, U57.1
Y452: J113.5, U57.12
Y453: J113.6, U57.15
Y454: J113.7, U57.14
Y455: J113.8, U57.13
Y456: J115.1, U58.4
Y457: J115.2, U58.2
Y458: J115.3, U58.5
Y459: J115.4, U58.1
Y460: J115.5, U58.12
Y461: J115.6, U58.15
Y462: J115.7, U58.14
Y463: J115.8, U58.13
Y464: J117.1, U59.4
Y465: J117.2, U59.2
Y466: J117.3, U59.5
Y467: J117.4, U59.1
Y468: J117.5, U59.12
Y469: J117.6, U59.15
Y470: J117.7, U59.14
Y471: J117.8, U59.13
Y472: J119.1, U60.4
Y473: J119.2, U60.2
Y474: J119.3, U60.5
Y475: J119.4, U60.1
Y476: J119.5, U60.12
Y477: J119.6, U60.15
Y478: J119.7, U60.14
Y479: J119.8, U60.13
Y480: J121.1, U61.4
Y481: J121.2, U61.2
Y482: J121.3, U61.5
Y483: J121.4, U61.1
Y484: J121.5, U61.12
Y485: J121.6, U61.15
Y486: J121.7, U61.14
Y487: J121.8, U61.13
Y488: J123.1, U62.4
Y489: J123.2, U62.2
Y490: J123.3, U62.5
Y491: J123.4, U62.1
Y492: J123.5, U62.12
Y493: J123.6, U62.15
Y494: J123.7, U62.14
Y495: J123.8, U62.13
Y496: J125.1, U63.4
Y497: J125.2, U63.2
Y498: J125.3, U63.5
Y499: J125.4, U63.1
Y500: J125.5, U63.12
Y501: J125.6, U63.15
Y502: J125.7, U63.14
Y503: J125.8, U63.13
Y504: J127.1, U64.4
Y505: J127.2, U64.2
Y506: J127.3, U64.5
Y507: J127.4, U64.1
Y508: J127.5, U64.12
Y509: J127.6, U64.15
Y510: J127.7, U64.14
Y511: J127.8, U64.13
Z: J2.5, U1.3
Z1: J4.5, U2.3
Z2: J6.5, U3.3
Z3: J8.5, U4.3
Z4: J10.5, U5.3
Z5: J12.5, U6.3
Z6: J14.5, U7.3
Z7: J16.5, U8.3
Z8: J18.5, U9.3
Z9: J20.5, U10.3
Z10: J22.5, U11.3
Z11: J24.5, U12.3
Z12: J26.5, U13.3
Z13: J28.5, U14.3
Z14: J30.5, U15.3
Z15: J32.5, U16.3
Z16: J34.5, U17.3
Z17: J36.5, U18.3
Z18: J38.5, U19.3
Z19: J40.5, U20.3
Z20: J42.5, U21.3
Z21: J44.5, U22.3
Z22: J46.5, U23.3
Z23: J48.5, U24.3
Z24: J50.5, U25.3
Z25: J52.5, U26.3
Z26: J54.5, U27.3
Z27: J56.5, U28.3
Z28: J58.5, U29.3
Z29: J60.5, U30.3
Z30: J62.5, U31.3
Z31: J64.5, U32.3
Z32: J66.5, U33.3
Z33: J68.5, U34.3
Z34: J70.5, U35.3
Z35: J72.5, U36.3
Z36: J74.5, U37.3
Z37: J76.5, U38.3
Z38: J78.5, U39.3
Z39: J80.5, U40.3
Z40: J82.5, U41.3
Z41: J84.5, U42.3
Z42: J86.5, U43.3
Z43: J88.5, U44.3
Z44: J90.5, U45.3
Z45: J92.5, U46.3
Z46: J94.5, U47.3
Z47: J96.5, U48.3
Z48: J98.5, U49.3
Z49: J100.5, U50.3
Z50: J102.5, U51.3
Z51: J104.5, U52.3
Z52: J106.5, U53.3
Z53: J108.5, U54.3
Z54: J110.5, U55.3
Z55: J112.5, U56.3
Z56: J114.5, U57.3
Z57: J116.5, U58.3
Z58: J118.5, U59.3
Z59: J120.5, U60.3
Z60: J122.5, U61.3
Z61: J124.5, U62.3
Z62: J126.5, U63.3
Z63: J128.5, U64.3

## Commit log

2016-04-18 Initial commit of hardware
2016-04-21 Resolving issues flagged on issue 1.
2016-04-21 Few changes after running the checklist.
2016-05-16 Fixing silkscreen, upping to v10
2016-05-16 Swapping 100k resistor out with 10k
2016-05-16 Schematic cleanup.
2016-05-17 created panel v10
2016-08-15 Bumping 0-width tDoc polygons up to 0.1mil.
2016-08-18 Readme standardization
2016-08-18 Adding example Arduino sketches.
2017-02-13 Used improved SparkFun libraries to remove the need for separate library. Removed single part library. Resolves #3
2022-05-18 Update Mux_Analog_Inputs.ino
    The changes in the code does the same thing but uses the defined variable for A0 to avoid confusion based on customer feedback.
